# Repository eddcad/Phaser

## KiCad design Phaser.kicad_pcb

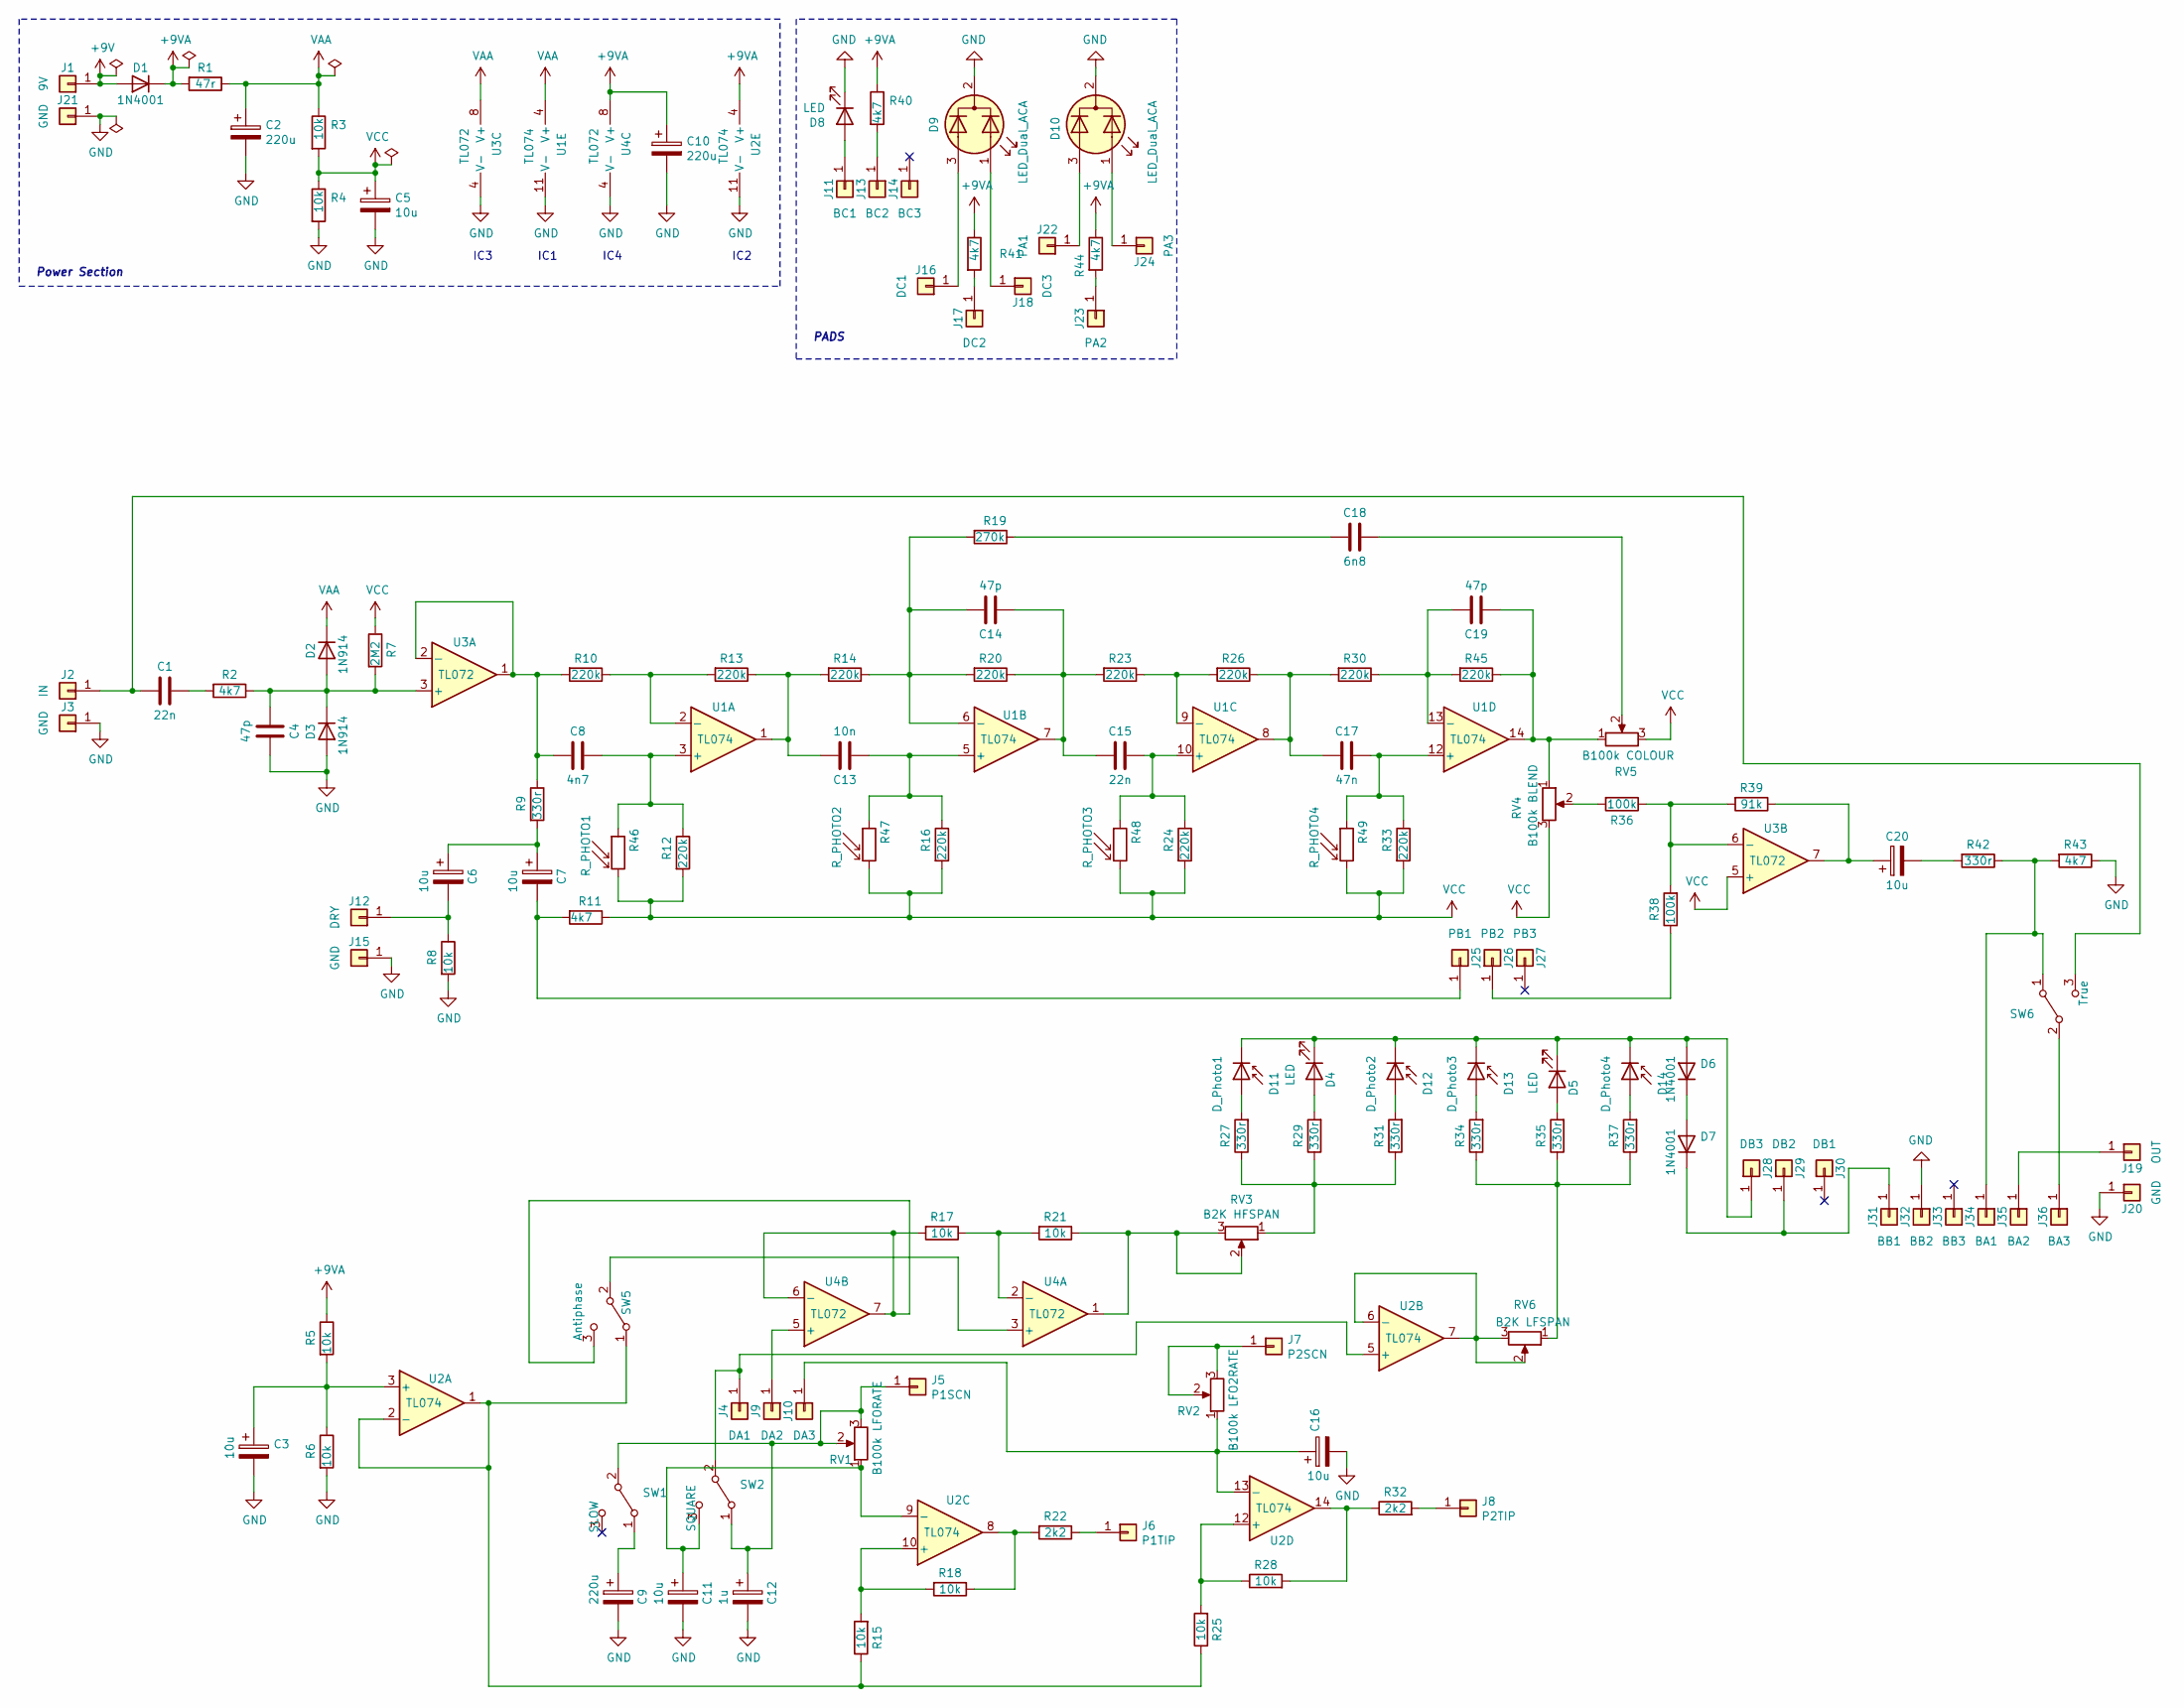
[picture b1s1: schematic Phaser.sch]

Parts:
C1, C15: 22n; C_Rect_L7.0mm_W2.5mm_P5.00mm
C2, C9, C10: 220u; CP_Radial_D8.0mm_P3.50mm
C3, C5, C6, C7, C11, C16, C20: 10u; CP_Radial_D5.0mm_P2.00mm
C4, C14: 47p; C_Disc_D4.7mm_W2.5mm_P5.00mm
C8: 4n7; C_Rect_L7.0mm_W2.5mm_P5.00mm
C12: 1u; CP_Radial_D5.0mm_P2.00mm
C13: 10n; C_Rect_L7.0mm_W2.5mm_P5.00mm
C17: 47n; C_Rect_L7.0mm_W2.5mm_P5.00mm
C18: 6n8; C_Rect_L7.0mm_W2.5mm_P5.00mm
C19: 47p; C_Rect_L7.0mm_W2.5mm_P5.00mm
D1, D6, D7: 1N4001; D_DO-41_SOD81_P10.16mm_Horizontal
D2, D3: 1N914; D_DO-35_SOD27_P7.62mm_Horizontal
D4, D5, D8: LED; LED_D5.0mm
D9, D10: LED_Dual_ACA; LED_D5.0mm-3
D11: D_Photo1; LED_D5.0mm
D12: D_Photo2; LED_D5.0mm
D13: D_Photo3; LED_D5.0mm
D14: D_Photo4; LED_D5.0mm
J1: 9V; SolderWire-0.25sqmm_1x01_D0.65mm_OD1.7mm
J2: IN; SolderWire-0.25sqmm_1x01_D0.65mm_OD1.7mm
J3, J15, J20, J21: GND; SolderWire-0.25sqmm_1x01_D0.65mm_OD1.7mm
J4: DA1; SolderWire-0.25sqmm_1x01_D0.65mm_OD1.7mm
J5: P1SCN; SolderWire-0.25sqmm_1x01_D0.65mm_OD1.7mm
J6: P1TIP; SolderWire-0.25sqmm_1x01_D0.65mm_OD1.7mm
J7: P2SCN; SolderWire-0.25sqmm_1x01_D0.65mm_OD1.7mm
J8: P2TIP; SolderWire-0.25sqmm_1x01_D0.65mm_OD1.7mm
J9: DA2; SolderWire-0.25sqmm_1x01_D0.65mm_OD1.7mm
J10: DA3; SolderWire-0.25sqmm_1x01_D0.65mm_OD1.7mm
J11: BC1; SolderWire-0.25sqmm_1x01_D0.65mm_OD1.7mm
J12: DRY; SolderWire-0.25sqmm_1x01_D0.65mm_OD1.7mm
J13: BC2; SolderWire-0.25sqmm_1x01_D0.65mm_OD1.7mm
J14: BC3; SolderWire-0.25sqmm_1x01_D0.65mm_OD1.7mm
J16: DC1; SolderWire-0.25sqmm_1x01_D0.65mm_OD1.7mm
J17: DC2; SolderWire-0.25sqmm_1x01_D0.65mm_OD1.7mm
J18: DC3; SolderWire-0.25sqmm_1x01_D0.65mm_OD1.7mm
J19: OUT; SolderWire-0.25sqmm_1x01_D0.65mm_OD1.7mm
J22: PA1; SolderWire-0.25sqmm_1x01_D0.65mm_OD1.7mm
J23: PA2; SolderWire-0.25sqmm_1x01_D0.65mm_OD1.7mm
J24: PA3; SolderWire-0.25sqmm_1x01_D0.65mm_OD1.7mm
J25: PB1; SolderWire-0.25sqmm_1x01_D0.65mm_OD1.7mm
J26: PB2; SolderWire-0.25sqmm_1x01_D0.65mm_OD1.7mm
J27: PB3; SolderWire-0.25sqmm_1x01_D0.65mm_OD1.7mm
J28: DB3; SolderWire-0.25sqmm_1x01_D0.65mm_OD1.7mm
J29: DB2; SolderWire-0.25sqmm_1x01_D0.65mm_OD1.7mm
J30: DB1; SolderWire-0.25sqmm_1x01_D0.65mm_OD1.7mm
J31: BB1; SolderWire-0.25sqmm_1x01_D0.65mm_OD1.7mm
J32: BB2; SolderWire-0.25sqmm_1x01_D0.65mm_OD1.7mm
J33: BB3; SolderWire-0.25sqmm_1x01_D0.65mm_OD1.7mm
J34: BA1; SolderWire-0.25sqmm_1x01_D0.65mm_OD1.7mm
J35: BA2; SolderWire-0.25sqmm_1x01_D0.65mm_OD1.7mm
J36: BA3; SolderWire-0.25sqmm_1x01_D0.65mm_OD1.7mm
R1: 47r; R_Axial_DIN0207_L6.3mm_D2.5mm_P7.62mm_Horizontal
R2, R11, R40, R41, R43, R44: 4k7; R_Axial_DIN0207_L6.3mm_D2.5mm_P7.62mm_Horizontal
R3, R4, R5, R6, R8, R15, R17, R18, R21, R25, R28: 10k; R_Axial_DIN0207_L6.3mm_D2.5mm_P7.62mm_Horizontal
R7: 2M2; R_Axial_DIN0207_L6.3mm_D2.5mm_P7.62mm_Horizontal
R9, R27, R29, R31, R34, R35, R37, R42: 330r; R_Axial_DIN0207_L6.3mm_D2.5mm_P7.62mm_Horizontal
R10, R12, R13, R14, R16, R20, R23, R24, R26, R30, R33, R45: 220k; R_Axial_DIN0207_L6.3mm_D2.5mm_P7.62mm_Horizontal
R19: 270k; R_Axial_DIN0207_L6.3mm_D2.5mm_P7.62mm_Horizontal
R22, R32: 2k2; R_Axial_DIN0207_L6.3mm_D2.5mm_P7.62mm_Horizontal
R36, R38: 100k; R_Axial_DIN0207_L6.3mm_D2.5mm_P7.62mm_Horizontal
R39: 91k; R_Axial_DIN0207_L6.3mm_D2.5mm_P7.62mm_Horizontal
R46: R_PHOTO1; R_LDR_5.2x5.2mm_P3.5mm_Horizontal
R47: R_PHOTO2; R_LDR_5.2x5.2mm_P3.5mm_Horizontal
R48: R_PHOTO3; R_LDR_5.2x5.2mm_P3.5mm_Horizontal
R49: R_PHOTO4; R_LDR_5.2x5.2mm_P3.5mm_Horizontal
RV1: B100k LFORATE; Potentiometer_Omeg_PC16BU_Vertical
RV2: B100k LFO2RATE; Potentiometer_Omeg_PC16BU_Vertical
RV3: B2K HFSPAN; Potentiometer_Omeg_PC16BU_Vertical
RV4: B100k BLEND; Potentiometer_Omeg_PC16BU_Vertical
RV5: B100k COLOUR; Potentiometer_Omeg_PC16BU_Vertical
RV6: B2K LFSPAN; Potentiometer_Omeg_PC16BU_Vertical
SW1: SLOW; SWITCH_SPDT_PTH_12.9X6.9MM
SW2: SQUARE; SWITCH_SPDT_PTH_12.9X6.9MM
SW5: Antiphase; SWITCH_SPDT_PTH_12.9X6.9MM
SW6: True; SWITCH_SPDT_PTH_12.9X6.9MM
U1, U2: TL074; DIP-14_W7.62mm
U3, U4: TL072; DIP-8_W7.62mm

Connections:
+9V: D1.2 (A), J1.1
+9VA: C10.1, D1.1 (K), R1.2, R5.1, R40.1, R41.1, R44.1, U2.4 (V+), U4.8 (V+)
GND: C2.2, C3.2, C4.1, C5.2, C9.2, C10.2, C11.2, C12.2, C16.2, D3.2 (A), D8.1 (K), D9.2 (K), D10.2 (K), J3.1, J15.1, J20.1, J21.1, J32.1, R4.2, R6.2, R8.2, R43.1, U1.11 (V-), U2.11 (V-), U3.4 (V-), U4.4 (V-)
unnamed: C1.1, R2.2
unnamed: C1.2, J2.1, SW6.3 (C)
unnamed: C3.1, R5.2, R6.1, U2.3 (+)
unnamed: C4.2, D2.2 (A), D3.1 (K), R2.1, R7.2, U3.3 (+)
unnamed: C6.1, C7.1, R9.2
unnamed: C6.2, J12.1, R8.1
unnamed: C7.2, J25.1, R11.2
unnamed: C8.1, R12.1, R46.1, U1.3 (+)
unnamed: C8.2, R9.1, R10.2, U3.1, U3.2 (-)
unnamed: C9.1, SW1.1 (A)
unnamed: C11.1, RV1.1, SW2.3 (C), U2.9 (-)
unnamed: C12.1, J5.1, RV1.2, RV1.3, SW1.2 (B), SW2.1 (A)
unnamed: C13.1, R13.1, R14.2, U1.1
unnamed: C13.2, R16.1, R47.1, U1.5 (+)
unnamed: C14.1, R14.1, R19.2, R20.2, U1.6 (-)
unnamed: C14.2, C15.2, R20.1, R23.2, U1.7
unnamed: C15.1, R24.1, R48.1, U1.10 (+)
unnamed: C16.1, J10.1, RV2.1, U2.13 (-)
unnamed: C17.1, R33.1, R49.1, U1.12 (+)
unnamed: C17.2, R26.1, R30.2, U1.8
unnamed: C18.1, RV5.2
unnamed: C18.2, R19.1
unnamed: C19.1, R30.1, R45.2, U1.13 (-)
unnamed: C19.2, R45.1, RV4.1, RV5.1, U1.14
unnamed: C20.1, R39.1, U3.7
unnamed: C20.2, R42.2
unnamed: D4.2 (A), R29.2
unnamed: D5.2 (A), R35.2
unnamed: D6.1 (K), D7.2 (A)
unnamed: D7.1 (K), J29.1, J31.1
unnamed: D8.2 (A), J11.1
unnamed: D9.1 (A1), J18.1
unnamed: D9.3 (A2), J16.1
unnamed: D10.1 (A1), J24.1
unnamed: D10.3 (A2), J22.1
unnamed: D4.1 (K), D5.1 (K), D6.2 (A), D11.1 (K), D12.1 (K), D13.1 (K), D14.1 (K), J28.1
unnamed: D11.2 (A), R27.2
unnamed: D12.2 (A), R31.2
unnamed: D13.2 (A), R34.2
unnamed: D14.2 (A), R37.2
unnamed: J4.1, SW2.2 (B), U2.5 (+)
unnamed: J6.1, R22.1
unnamed: J7.1, RV2.2, RV2.3
unnamed: J8.1, R32.2
unnamed: J9.1, U4.5 (+)
unnamed: J13.1, R40.2
unnamed: J17.1, R41.2
unnamed: J19.1, J35.1
unnamed: J23.1, R44.2
unnamed: J26.1, R38.1
unnamed: J34.1, R42.1, R43.2, SW6.1 (A)
unnamed: J36.1, SW6.2 (B)
unnamed: R10.1, R13.2, U1.2 (-)
unnamed: R15.1, R25.1, SW5.1 (A), U2.1, U2.2 (-)
unnamed: R15.2, R18.2, U2.10 (+)
unnamed: R17.1, R21.2, U4.2 (-)
unnamed: R17.2, SW5.3 (C), U4.6 (-), U4.7
unnamed: R18.1, R22.2, U2.8
unnamed: R21.1, RV3.2, RV3.3, U4.1
unnamed: R23.1, R26.2, U1.9 (-)
unnamed: R25.2, R28.1, U2.12 (+)
unnamed: R27.1, R29.1, R31.1, RV3.1
unnamed: R28.2, R32.1, U2.14
unnamed: R34.1, R35.1, R37.1, RV6.1
unnamed: R36.1, R38.2, R39.2, U3.6 (-)
unnamed: R36.2, RV4.2
unnamed: RV6.2, RV6.3, U2.6 (-), U2.7
unnamed: SW5.2 (B), U4.3 (+)
VAA: C2.1, D2.1 (K), R1.1, R3.1, U1.4 (V+), U3.8 (V+)
VCC: C5.1, R3.2, R4.1, R7.1, R11.1, R12.2, R16.2, R24.2, R33.2, R46.2, R47.2, R48.2, R49.2, RV4.3, RV5.3, U3.5 (+)

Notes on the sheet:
IC3
IC1
IC4
IC2
Power Section
PADS

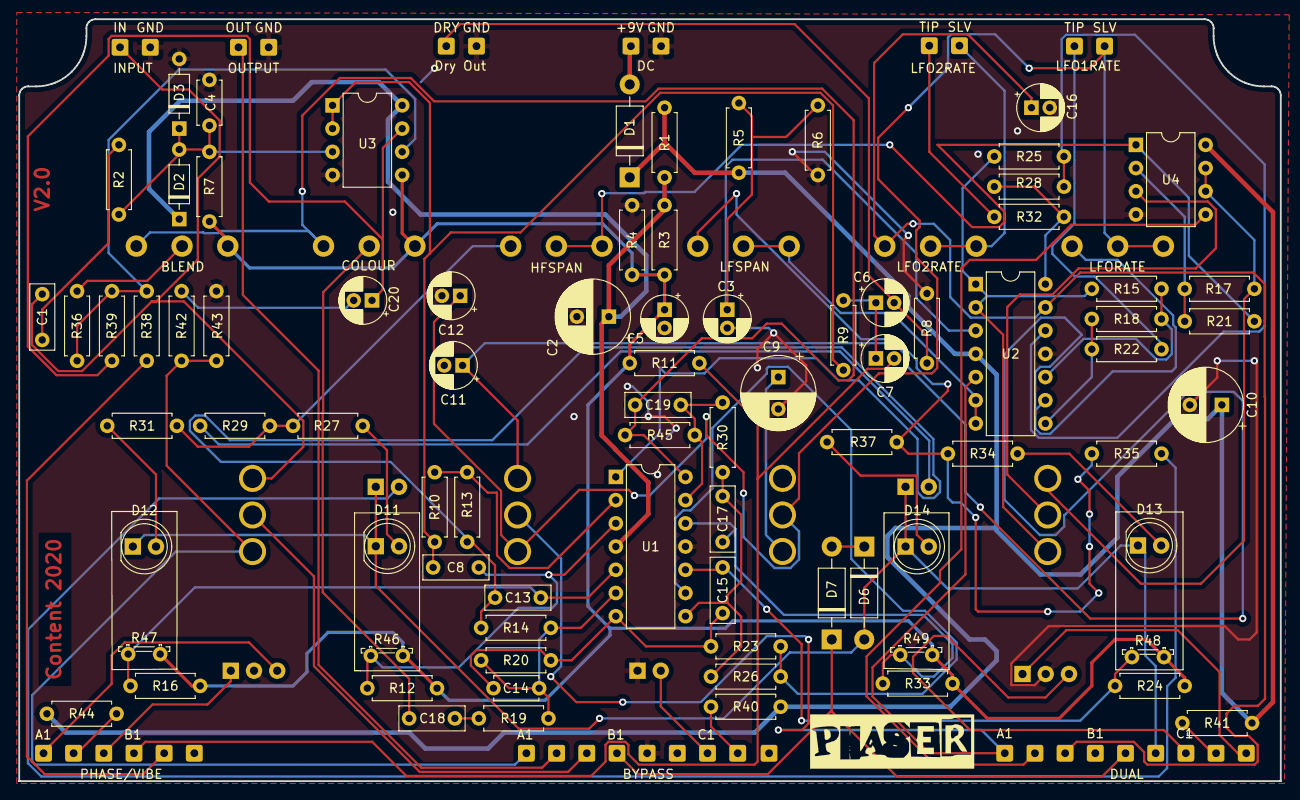
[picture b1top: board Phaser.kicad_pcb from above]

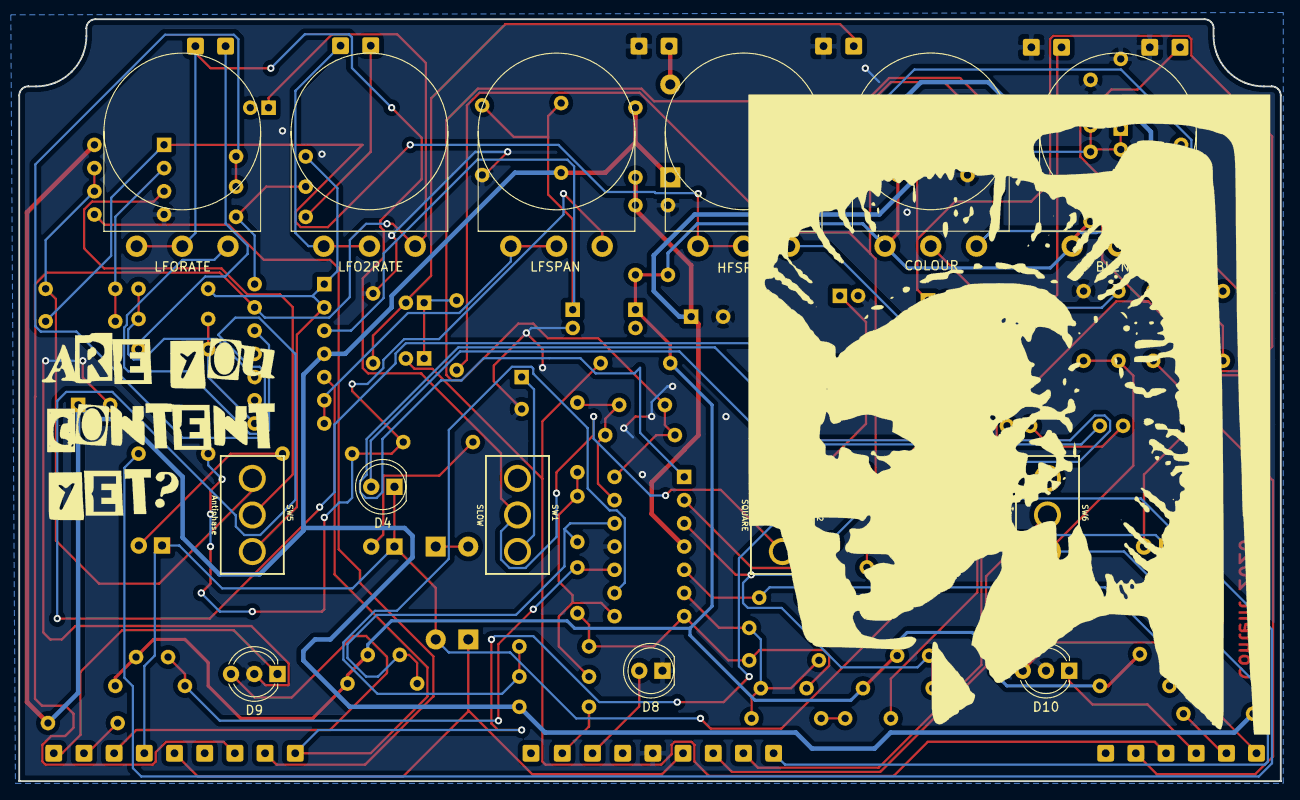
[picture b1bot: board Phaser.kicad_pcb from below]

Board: 2 copper layers, 138.0 x 83.3 mm, 133 parts (15 on the bottom side), 73 nets.

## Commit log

2020-09-18 Fixed initial errors and laid out 1590XX pcb
2020-09-19 Preliminary XX board layout
2020-09-19 Deleted connection between R31 R34
2020-09-20 Provisional Phaser V2.0 completion
2020-09-20 Initial Commit for V2.1
2020-10-09 Cleaned up Silks
2020-11-11 Added license
